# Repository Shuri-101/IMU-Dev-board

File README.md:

# IMU STM32STM32G431CBT6 DEV BOARD:

Hello, this is just a project for me to get some experience and learn about data busses like SPI (Serial Peripheral Interface), UART (Universal Asynchronous Receiver/Transmitter) and I2C (Inter-Integrated Circuit) and learn how to program sensors like IMUs, barometers, altimeters, GPS etc. This because I hope to design a flight computer for a drone or active stabilized rocket so yeah. 

## PCB
### About the board:

This board contains: 
- IMU (LSM6DS3TR-C)
- x6 GPIO headers
- x2 I2C headers (I2C 1 and I2C 2)
- x1 UART header (UART2)
- x2 SPI Headers (SPI 2, SPI3)
- x2 ADC headers
- x2 PWM headers
- x2 5V headers
- x4 3.3V headers
- x6 GND headers

### Schematic:

Since I had 48pins on my MCU I thought might as well use them and connect them to headers so I can use them later to connect other sensors and stuff.

Note for beginners: Decoupling capacitors are meant to smooth out power spikes and dips that might cause logic errors in the MCU, they also act as filtering capacitors keeping noise off sensitive rails like analogue (noise is unwanted voltage that you did not put there) as analogue data is the measure of voltage. 

Example of my decoupling capacitors are: 

Note that the capacitors are placed in parallel to the 3V3 line. 4.7uF is a bulk capacitors meant to refill the small capacitors between the spikes and dips that get drained very quickly during the spikes and dips. 

For more info about decoupling watch: 
https://www.youtube.com/watch?v=u40kX1DYKdA

### Why I chose these parts?

- I chosen the STM32STM32G431CBTX since it offered FPU, CRC and a mathematical accelerator which are needed to control these sensors, I chosen the LQFP-48 package since its easier to solder and it was the only variant available to buy at the time.
- FPU, a floating point unit allows you to work with floating point numbers such as a fraction, decimals etc 100x faster than a MCU without a FPU, since sensors output raw numbers that need to converted into data requires floating point maths hundreds of times per second.
- DSP, Digital Signal Processing lets you do fast repeated multiply-and-add on a stream of numbers, which is needed to do maths for the sensors roughly twice as fast than a MCU without it.

- I chose the LSM6DS3TR-C as its cheap has 6 axis and a +/- 2000 degrees / second and it has +/- 16g which works for learning how to program and design a PCB for an IMU. 

### Layers

#### Layer 1 (Main signal routing layer)
- In this layer I routed most of my signals + decupling / filtering capcitors (since they need to be placed as close to the thing its meant to decoupling / filter around 5mm max) taking care to have proper clearance from aggressive signals such as SCK to avoid crosstalk and interference from other signals.
- I also used local copper pours to create a low impedance route to GND.
- LDO is placed far away from IMU at the opposite end of the board to prevent the heat it generates from interfering with the readings.

#### Layer 2 (Ground Plane):
- This layer is a layer of copper connected ground aka "ground plane" and offers a low impedance path (simple terms path of low total resistance) to GND and also acts as a reference plane for signal return currents.
- Notice I have not routed anything on this layer, this is to maintain a unbroken reference plane otherwise signal return currents will have to loop around interfering with other signals.
- Using a ground plane also makes way way way easier to route your GND traces instead of using long traces back to power supply.

#### Layer 3 (3V3 Power Plane):
- This layer is another layer of copper but this time its connected to 3V3 from my LOW Dropout Converter which converts 5V --> 3.3V cause MCUs and my IMU runs on 3.3v logic.
- The 3v3 plane makes it easier to route my power supplies to my components that need it as its saves room as you can see from the picture I just use vias to route up from the plane to the MCU.
- Here you can see I routed signals here because I had no other choice as this board is quite small, this inevitably caused islands of copper to form on the PCB meaning I had to create localised copper pours on layer 3 to stitch these islands togther.

#### Layer 4 (3V3 stitching and Signal routing):
- In this layer I also used it to route signals I could not route on other layers as I had no room.
- I also used this layer to stitch the 3V3 plane up.
- The signals on this layer references with the 3V3 power plane because decoupling capacitors tie 3V3 and GND together.

## BOM:
To get these parts I recommend LCSC since they offer cheap global shipping and are available with JLCPCB assemble option.
To get these parts simply type the LSCC part code into the search bar of their website.
#### Parts:
USING LCSC:
- C967633: IMU

- C529355: MCU

- C6186: LDO

- C20608785: YELLOW LED

- C2894893: USB-C PORT

- C19171391: RED LED

- C33546008: 22uF MLCC XR5 (Filtering)

- C36911367: 100nF MLCC XR7 (Decoupling)

- C107365: 4.7uF MLCC XR7 (Bulk decoupling)

- C53282227: 1uF MLCC XR7

- C519909: 10nF MLCC XR7

- C118848: 5.1K Resistor

- C54921199: 470 Resistor

- C54921203: 4.7K Resistor

- C54921094: 10K Resistor

#### Estimated total for components:

#### PCB manufacturing costs:

#### TOTAL:
TOTAL COSTS: $54.03

## Firmware:
Since I don't know how to code in C and as I mentioned at the start this board is meant to get me to learn how to code, ill just send the config file for the IMU pins ONLY since I dont know what other things I want to plug into the board yet, and that is decide by the end user, but I'll set up the main configs for the MCU like clock SWD(for programming) and pins for the IMU. Also will need to learn fully about clocks, how they work, and how to configure data lines in CUBE MX...

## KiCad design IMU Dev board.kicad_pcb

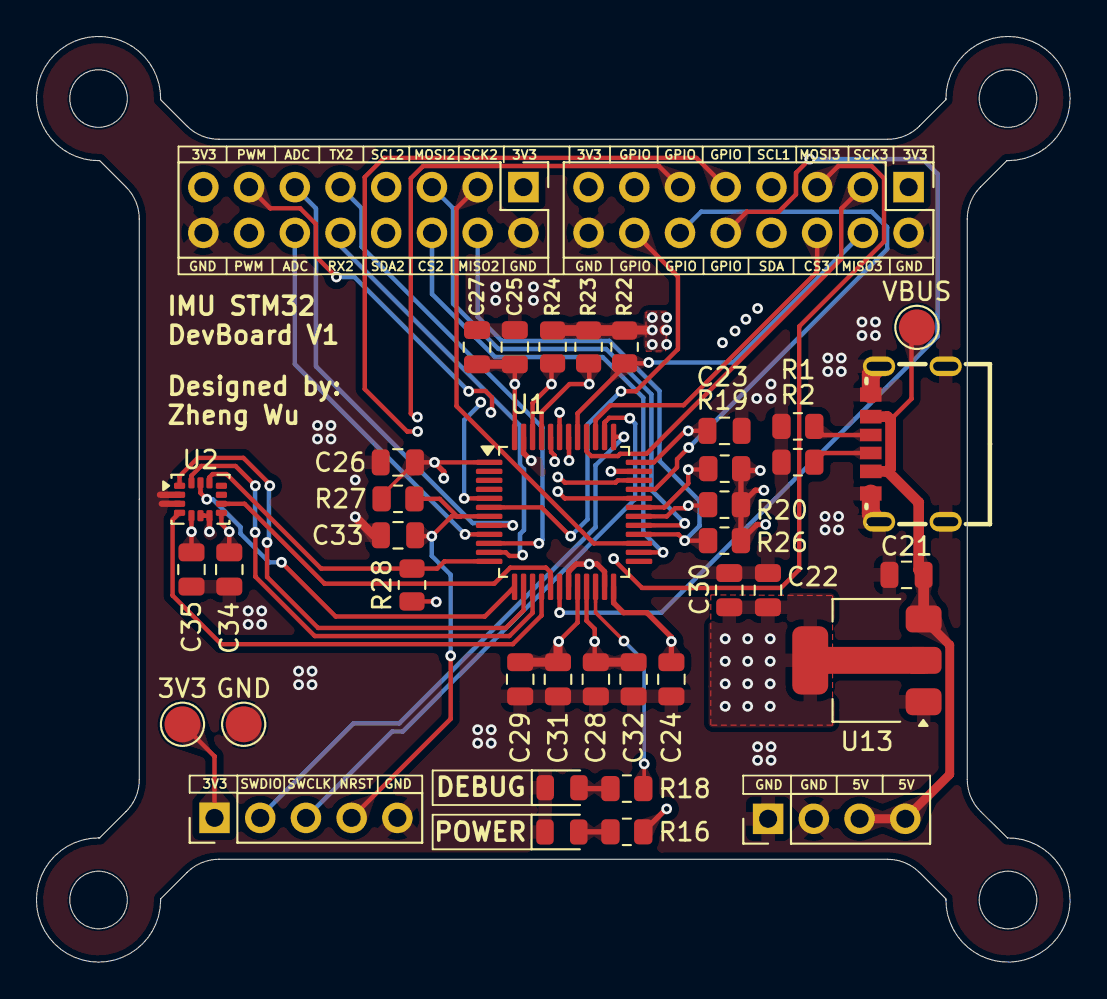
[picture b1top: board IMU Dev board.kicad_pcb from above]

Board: 4 copper layers, 57.4 x 51.4 mm, 44 parts (0 on the bottom side), 41 nets.

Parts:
3V3: TestPoint; TestPoint_Pad_D2.0mm
C21, C22: 22uF; C_0805_2012Metric
C23, C24, C25, C26, C28, C30, C33, C34, C35: 100nF; C_0805_2012Metric
C27: 4.7uF; C_0805_2012Metric
C29, C32: 1uF; C_0805_2012Metric
C31: 10nF; C_0805_2012Metric
DEBUG: YELLOW; LED_0805_2012Metric
GND: TestPoint; TestPoint_Pad_D2.0mm
H1, H2, H3, H4: MountingHole; MountingHole_3.2mm_M3
J1: Conn_01x05_Pin; PinHeader_1x05_P2.54mm_Vertical
J3, J4: Conn_02x08_Odd_Even; PinHeader_2x08_P2.54mm_Vertical
J7: Conn_01x04_Pin; PinHeader_1x04_P2.54mm_Vertical
POWER: GREEN; LED_0805_2012Metric
R1, R2: 5.1K; R_0805_2012Metric
R16, R18: 470; R_0805_2012Metric
R19, R20, R23, R24: 4.7k; R_0805_2012Metric
R22, R26, R27, R28: 10k; R_0805_2012Metric
U1: STM32G431CBTx; LQFP-48_7x7mm_P0.5mm
U2: LSM6DS3TR-C (Pin 7 --> GND); LGA-14_3x2.5mm_P0.5mm_LayoutBorder3x4y
U13: AMS1117-3.3; SOT-223-3_TabPin2
USB1: HC-TYPE-C-6P-01A; USB-C-SMD_HC-TYPE-C-6P-01A
VBUS: TestPoint; TestPoint_Pad_D2.0mm

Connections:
3V3: 3V3.1 (1_1), C22.1, C23.1, C24.1, C25.1, C26.1, C27.1, C28.1, C29.1, C30.2, C31.2, C32.1, C34.1, C35.1, J1.1, J3.1, J3.15, J4.1, J4.15, R16.1, R19.2, R20.2, R22.2, R23.2, R24.2, R26.2, R27.2, R28.2, U1.1 (VBAT), U1.20 (VREF+), U1.21 (VDDA), U1.24 (VDD), U1.36 (VDD), U1.48 (VDD), U2.5 (VDDIO), U2.8 (VDD), U13.2 (VO)
ADC PA0: J3.11, U1.8 (PA0)
ADC PA1: J3.12, U1.9 (PA1)
CS 1: R28.1, U1.12 (PA4), U2.12 (CS)
CS 2: J3.6, U1.26 (PB12)
CS 3: J4.6, U1.39 (PA15)
DEBUG_LED: R18.1, U1.22 (PB10)
GND: C21.1, C22.2, C23.2, C24.2, C25.2, C26.2, C27.2, C28.2, C29.2, C30.1, C31.1, C32.2, C33.2, C34.2, C35.2, DEBUG.1 (K), GND.1 (1_1), J1.5, J3.2, J3.16, J4.2, J4.16, J7.1, J7.2, POWER.1 (K), R1.2, R2.1, U1.19 (VSSA), U1.23 (VSS), U1.35 (VSS), U1.47 (VSS), U2.2 (SDX), U2.3 (SCX), U2.6 (GND), U2.7 (GND), U13.1 (GND), USB1.1, USB1.2, USB1.3, USB1.4, USB1.A12, USB1.B12
GPIO PA10: J4.9, U1.32 (PA10)
GPIO PA11: J4.12, U1.33 (PA11)
GPIO PA12: J4.11, U1.34 (PA12)
GPIO PB2: J4.10, U1.18 (PB2)
GPIO PF0: J4.13, U1.5 (PF0)
GPIO PF1: J4.14, U1.6 (PF1)
INT1: U1.16 (PB0), U2.4 (INT1)
INT2: U1.17 (PB1), U2.9 (INT2)
MISO 1: U1.14 (PA6), U2.1 (SDO/SA0)
MISO 2: J3.4, R26.1, U1.28 (PB14)
MISO 3: J4.4, R22.1, U1.41 (PB4)
MOSI 1: U1.15 (PA7), U2.14 (SDA)
MOSI 2: J3.5, U1.29 (PB15)
MOSI 3: J4.5, U1.42 (PB5)
NRST: C33.1, J1.4, R27.1, U1.7 (PG10)
unnamed: POWER.2 (A), R16.2
unnamed: DEBUG.2 (A), R18.2
unnamed: R1.1, USB1.B5
unnamed: R2.2, USB1.A5
PWM/RX IN 1: J3.14, U1.44 (PB7)
PWM/TX OUT 1: J3.13, U1.43 (PB6)
RX IN 2: J3.10, U1.11 (PA3)
SCK 1: U1.13 (PA5), U2.13 (SCL)
SCK 2: J3.3, U1.27 (PB13)
SCK 3: J4.3, U1.40 (PB3)
SCL 1: J4.7, R23.1, U1.45 (PB8)
SCL 2: J3.7, R19.1, U1.31 (PA9)
SDA 1: J4.8, R24.1, U1.46 (PB9)
SDA 2: J3.8, R20.1, U1.30 (PA8)
SWCLK: J1.3, U1.38 (PA14)
SWDIO: J1.2, U1.37 (PA13)
TX OUT 2: J3.9, U1.10 (PA2)
VBUS: C21.2, J7.3, J7.4, U13.3 (VI), USB1.A9, USB1.B9, VBUS.1 (1_1)

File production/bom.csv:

Designator,Footprint,Quantity,Value,LCSC Part #
"3V3, GND, VBUS",TestPoint_Pad_D2.0mm,3,TestPoint,
"C21, C22",0805,2,22uF,
"C23, C24, C25, C26, C28, C30, C33, C34, C35",0805,9,100nF,
C27,0805,1,4.7uF,
"C29, C32",0805,2,1uF,
C31,0805,1,10nF,
DEBUG,0805,1,YELLOW,C2296
J1,PinHeader_1x05_P2.54mm_Vertical,1,Conn_01x05_Pin,
"J3, J4",PinHeader_2x08_P2.54mm_Vertical,2,Conn_02x08_Odd_Even,
J7,PinHeader_1x04_P2.54mm_Vertical,1,Conn_01x04_Pin,C2691448
POWER,0805,1,GREEN,C2297
"R1, R2",0805,2,5.1K,
R16,0805,1,470,C23241
R18,0805,1,470,C21190
"R19, R20, R23, R24",0805,4,4.7k,C21190
"R22, R26, R27, R28",0805,4,10k,C21190
U1,LQFP-48_7x7mm_P0.5mm,1,STM32G431CBTx,
U13,SOT-223-3_TabPin2,1,AMS1117-3.3,C6186
U2,LGA-14_3x2.5mm_P0.5mm_LayoutBorder3x4y,1,LSM6DS3TR-C (Pin 7 --> GND),
USB1,USB-C-SMD_HC-TYPE-C-6P-01A,1,HC-TYPE-C-6P-01A,C2894893

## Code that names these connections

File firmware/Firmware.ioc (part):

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Mcu.Name=STM32G431C(6-8-B)Tx
Mcu.Package=LQFP48
Mcu.UserName=STM32G431CBTx
PA13.Mode=Serial_Wire
PA13.Signal=SYS_JTMS-SWDIO
PA14.Mode=Serial_Wire
PA14.Signal=SYS_JTCK-SWCLK
PA4.GPIOParameters=PinState,GPIO_PuPd,GPIO_Label
PA4.GPIO_Label=IMU-CS
PA4.GPIO_PuPd=GPIO_PULLUP
PA4.PinState=GPIO_PIN_SET
PA4.Signal=GPIO_Output
PA5.Mode=Full_Duplex_Master
PA5.Signal=SPI1_SCK
PA6.Mode=Full_Duplex_Master
PA6.Signal=SPI1_MISO
PA7.Mode=Full_Duplex_Master
PA7.Signal=SPI1_MOSI
PB0.GPIOParameters=GPIO_Label,GPIO_ModeDefaultEXTI
PB0.GPIO_Label=IMU-INT1
PB0.GPIO_ModeDefaultEXTI=GPIO_MODE_IT_RISING
PB0.Signal=GPXTI0
PB1.GPIOParameters=GPIO_Label
PB1.GPIO_Label=IMU-INT2
PB1.Signal=GPXTI1
PB10.Signal=GPIO_Output
RCC.HSE_VALUE=8000000
RCC.SYSCLKFreq_VALUE=170000000
RCC.SYSCLKSource=RCC_SYSCLKSOURCE_PLLCLK
board=custom
